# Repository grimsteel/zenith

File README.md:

# zenith

> A low cost USB-based FPV receiver/ground station

This was created to be used with [astra](https://github.com/TheScientist101/astra), a low cost FPV drone.

It features:
- A Seeed Studio RP2040 
- An RX5808

Inspired by the [rx5808-pro-diversity](https://github.com/sheaivey/rx5808-pro-diversity)

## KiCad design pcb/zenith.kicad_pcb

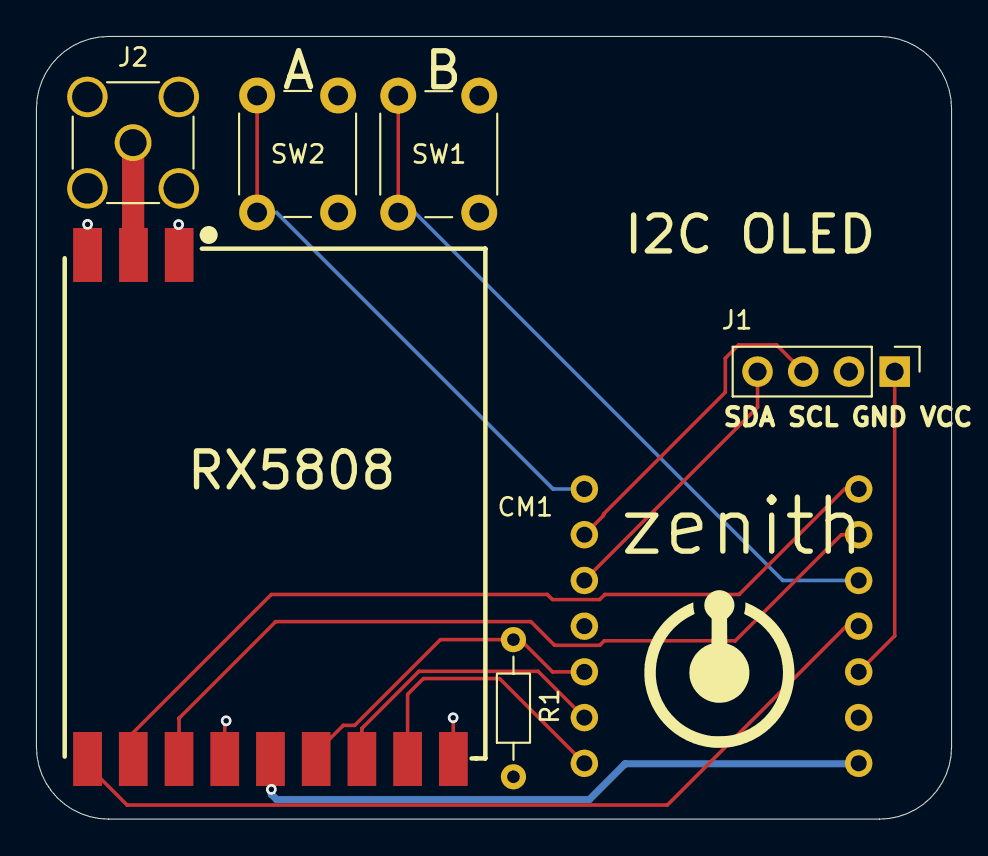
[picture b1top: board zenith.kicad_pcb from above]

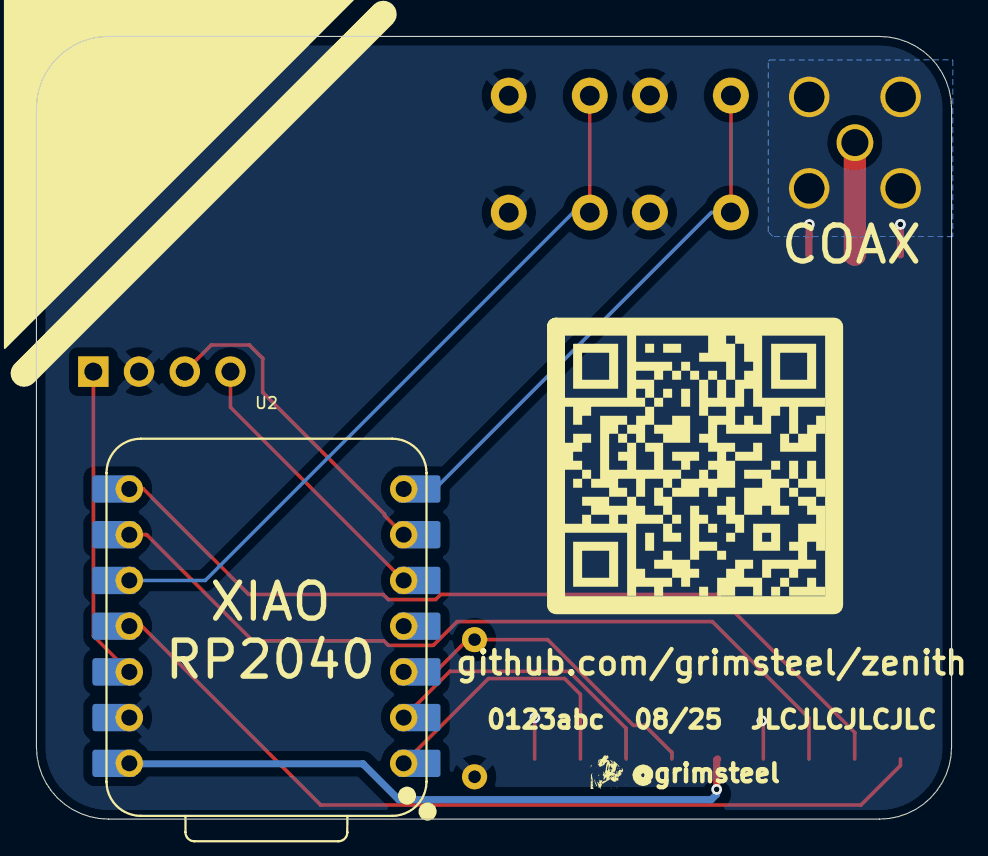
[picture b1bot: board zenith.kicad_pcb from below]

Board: 2 copper layers, 50.8 x 43.5 mm, 8 parts (2 on the bottom side), 14 nets.

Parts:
CM1: RX5808; COMM-SMD_12P_RX5808
J1: Conn_01x04_Pin; PinHeader_1x04_P2.54mm_Vertical
J2: Conn_Coaxial; SMA_Amphenol_901-144_Vertical
QR*****: https://github.com/grimsteel/zenith; qrcode
R1: 100k; R_Axial_DIN0204_L3.6mm_D1.6mm_P7.62mm_Horizontal
SW1, SW2: SW_Push; SW_PUSH_6mm
U2: XIAO-RP2040-DIP

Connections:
+3.3V: J1.1, U2.12 (3V3)
+5V: CM1.8 (+5V), U2.14 (VBUS)
ANT: CM1.2 (ANT), J2.1 (In)
AUDIO: CM1.10 (A6.5M), U2.2 (GPIO27/ADC1/A1)
BTN1: SW1.1, U2.10 (GPIO4/MISO)
BTN2: SW2.1, U2.7 (GPIO0/TX)
GND: CM1.1 (GND), CM1.3 (GND), CM1.7 (GND), CM1.12 (GND), J1.2, J2.2 (Ext), R1.1, SW1.2, SW2.2, U2.13 (GND)
MOSI: CM1.4 (CH1), U2.11 (GPIO3/MOSI)
RSSI: CM1.9 (RSSI), R1.2, U2.3 (GPIO28/ADC2/A2)
RX_CS: CM1.5 (CH2), U2.8 (GPIO1/RX)
SCK: CM1.6 (CH3), U2.9 (GPIO2/SCK)
SCL: J1.3, U2.6 (GPIO7/SCL)
SDA: J1.4, U2.5 (GPIO6/SDA)
VIDEO: CM1.11 (VIDEO), U2.1 (GPIO26/ADC0/A0)

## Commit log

2025-08-07 bom: add basic bom
2025-08-08 pcb: initial schematic + pcb
